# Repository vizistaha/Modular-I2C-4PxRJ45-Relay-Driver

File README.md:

# Modular-I2C-4PxRJ45-Relay-Driver
an oxrs compatible I2C-4PxRJ45-Relay-Driver board in a modular format. Inspired by 8-Channel Relay Driver Shield from Superhouse and Modular-I2CRJ45 from Austin's Creations.

rev 1 - non isolated version  
rev 2 - power circuit is fully isolated from mcu circuit by optocoupler  
rev 2_1 - output uses pluggable terminal instead of 4PxRJ45  
RJ45toTerminal - breakout board for rj45 to pluggable connector (check read me for pin mapping)

For more details about OXRS: https://oxrs.io/

Credits
-------
 * Austin's Creations <https://www.austinscreations.ca/>
 * Jonathan Oxer <https://www.superhouse.tv/>

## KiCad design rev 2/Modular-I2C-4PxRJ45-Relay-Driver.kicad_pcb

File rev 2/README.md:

# RJ45 Pinout

| Pin        | Pair       | Color        |
| ---------- |:----------:| ------------ |
| 1          | 1+         | Orange-White |
| 2          | 1-         | Orange       |
| 3          | 2+         | Green-White  |
| 6          | 2-         | Green        |
| 5          | 3+         | Blue-White   |
| 4          | 3-         | Blue         |
| 7          | 4+         | Brown-White  |
| 8          | 4-         | Brown        |

VIN Jumper Connection

| VIN        | JP1        | JP2     | JP3    |
| ---------- |:---------- | ------- | ------ |
| 24V        | VIN        | 5V      | ON     |
| 12V        | VIN        | 5V      | ON     |
| 5V         | VIN        | VIN     | OFF    |

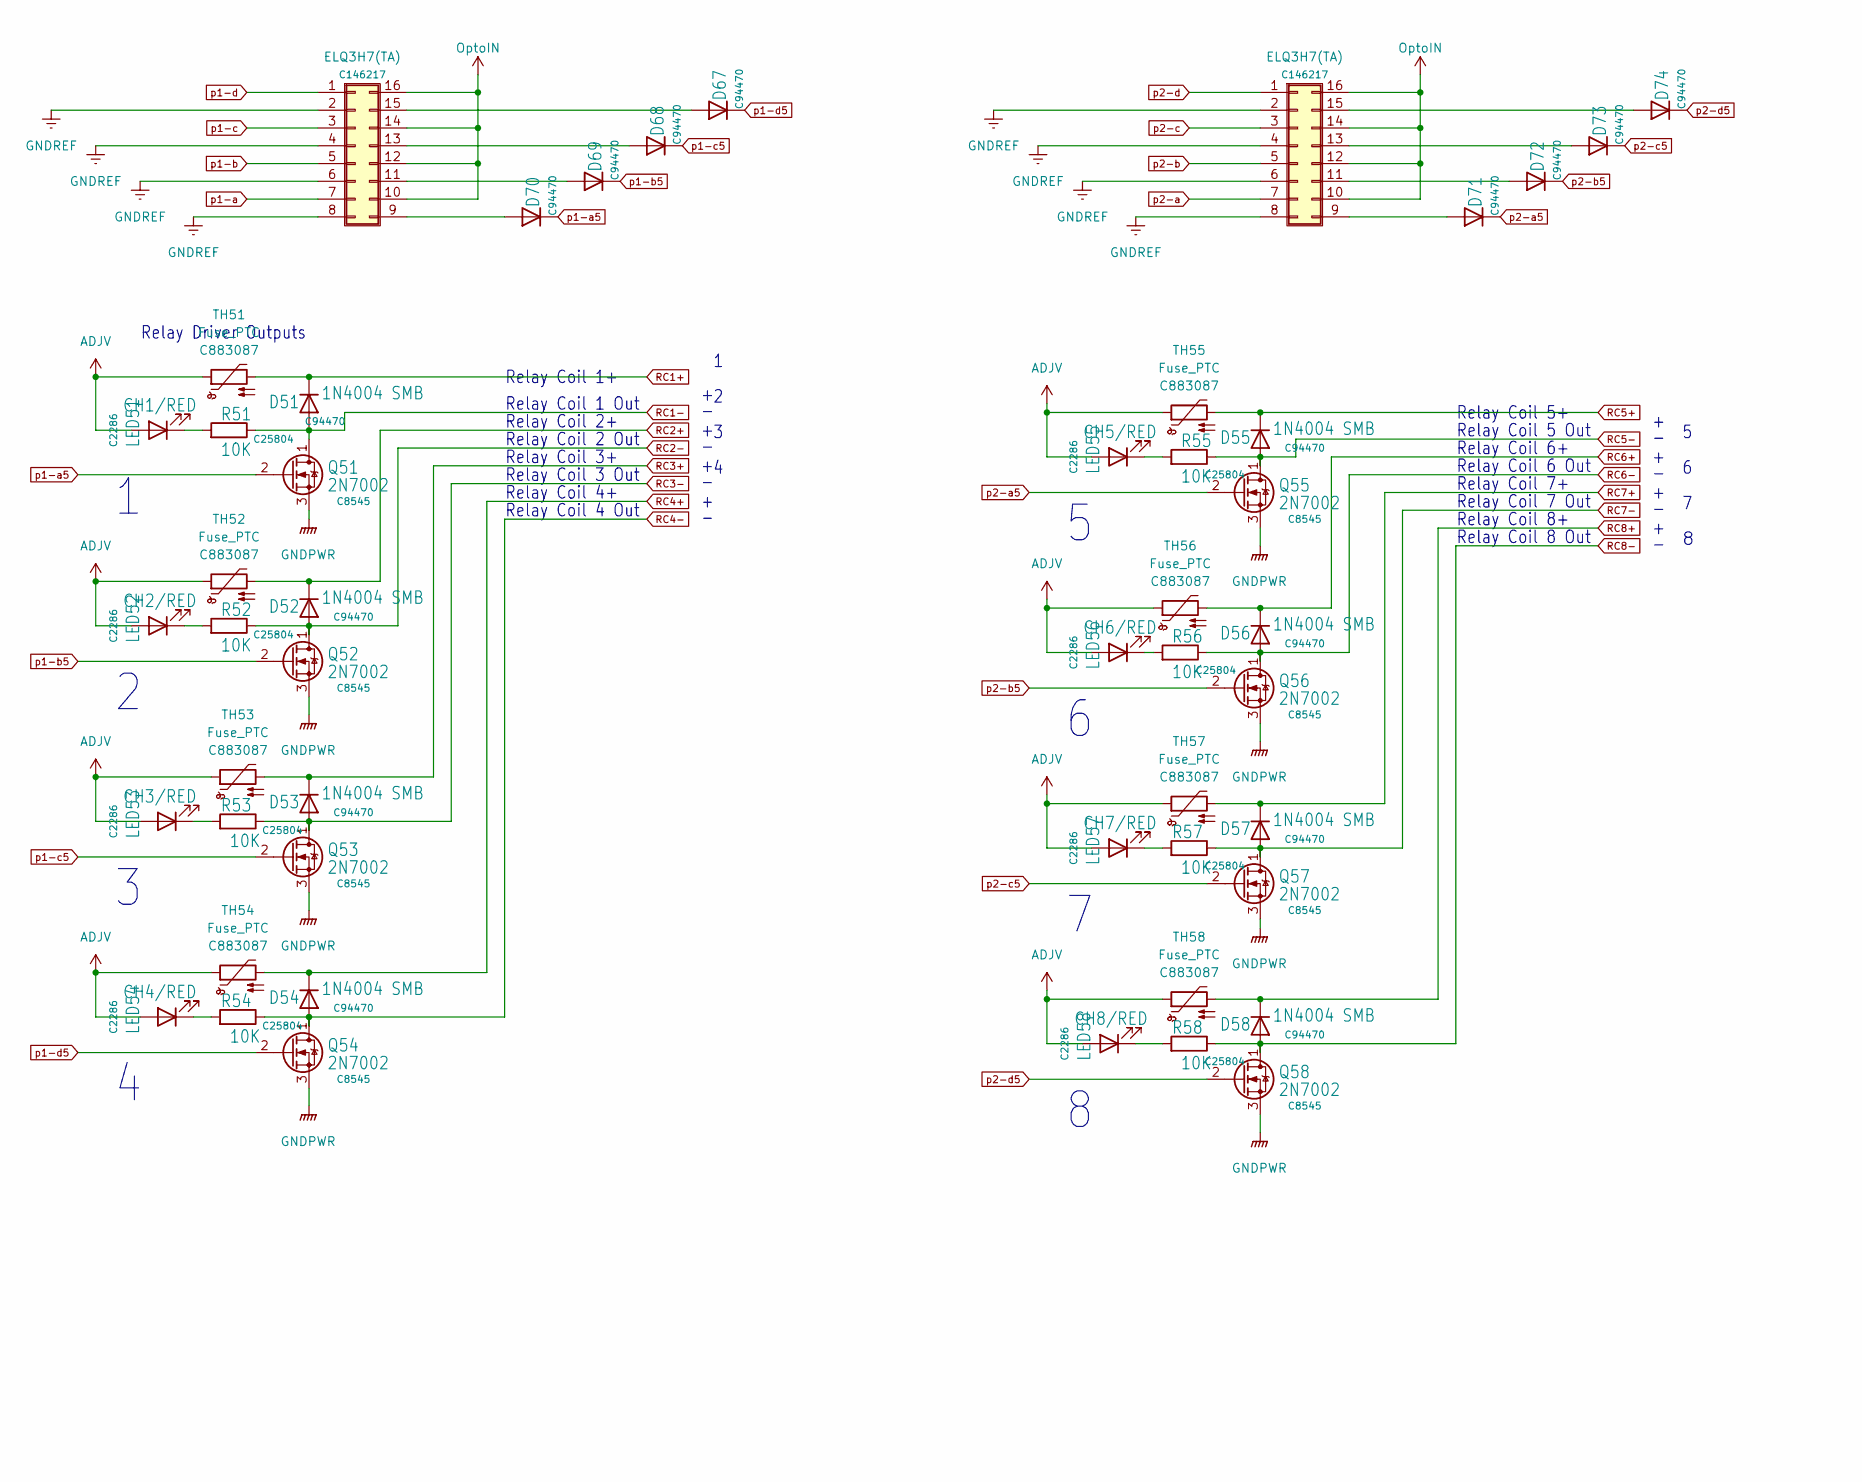
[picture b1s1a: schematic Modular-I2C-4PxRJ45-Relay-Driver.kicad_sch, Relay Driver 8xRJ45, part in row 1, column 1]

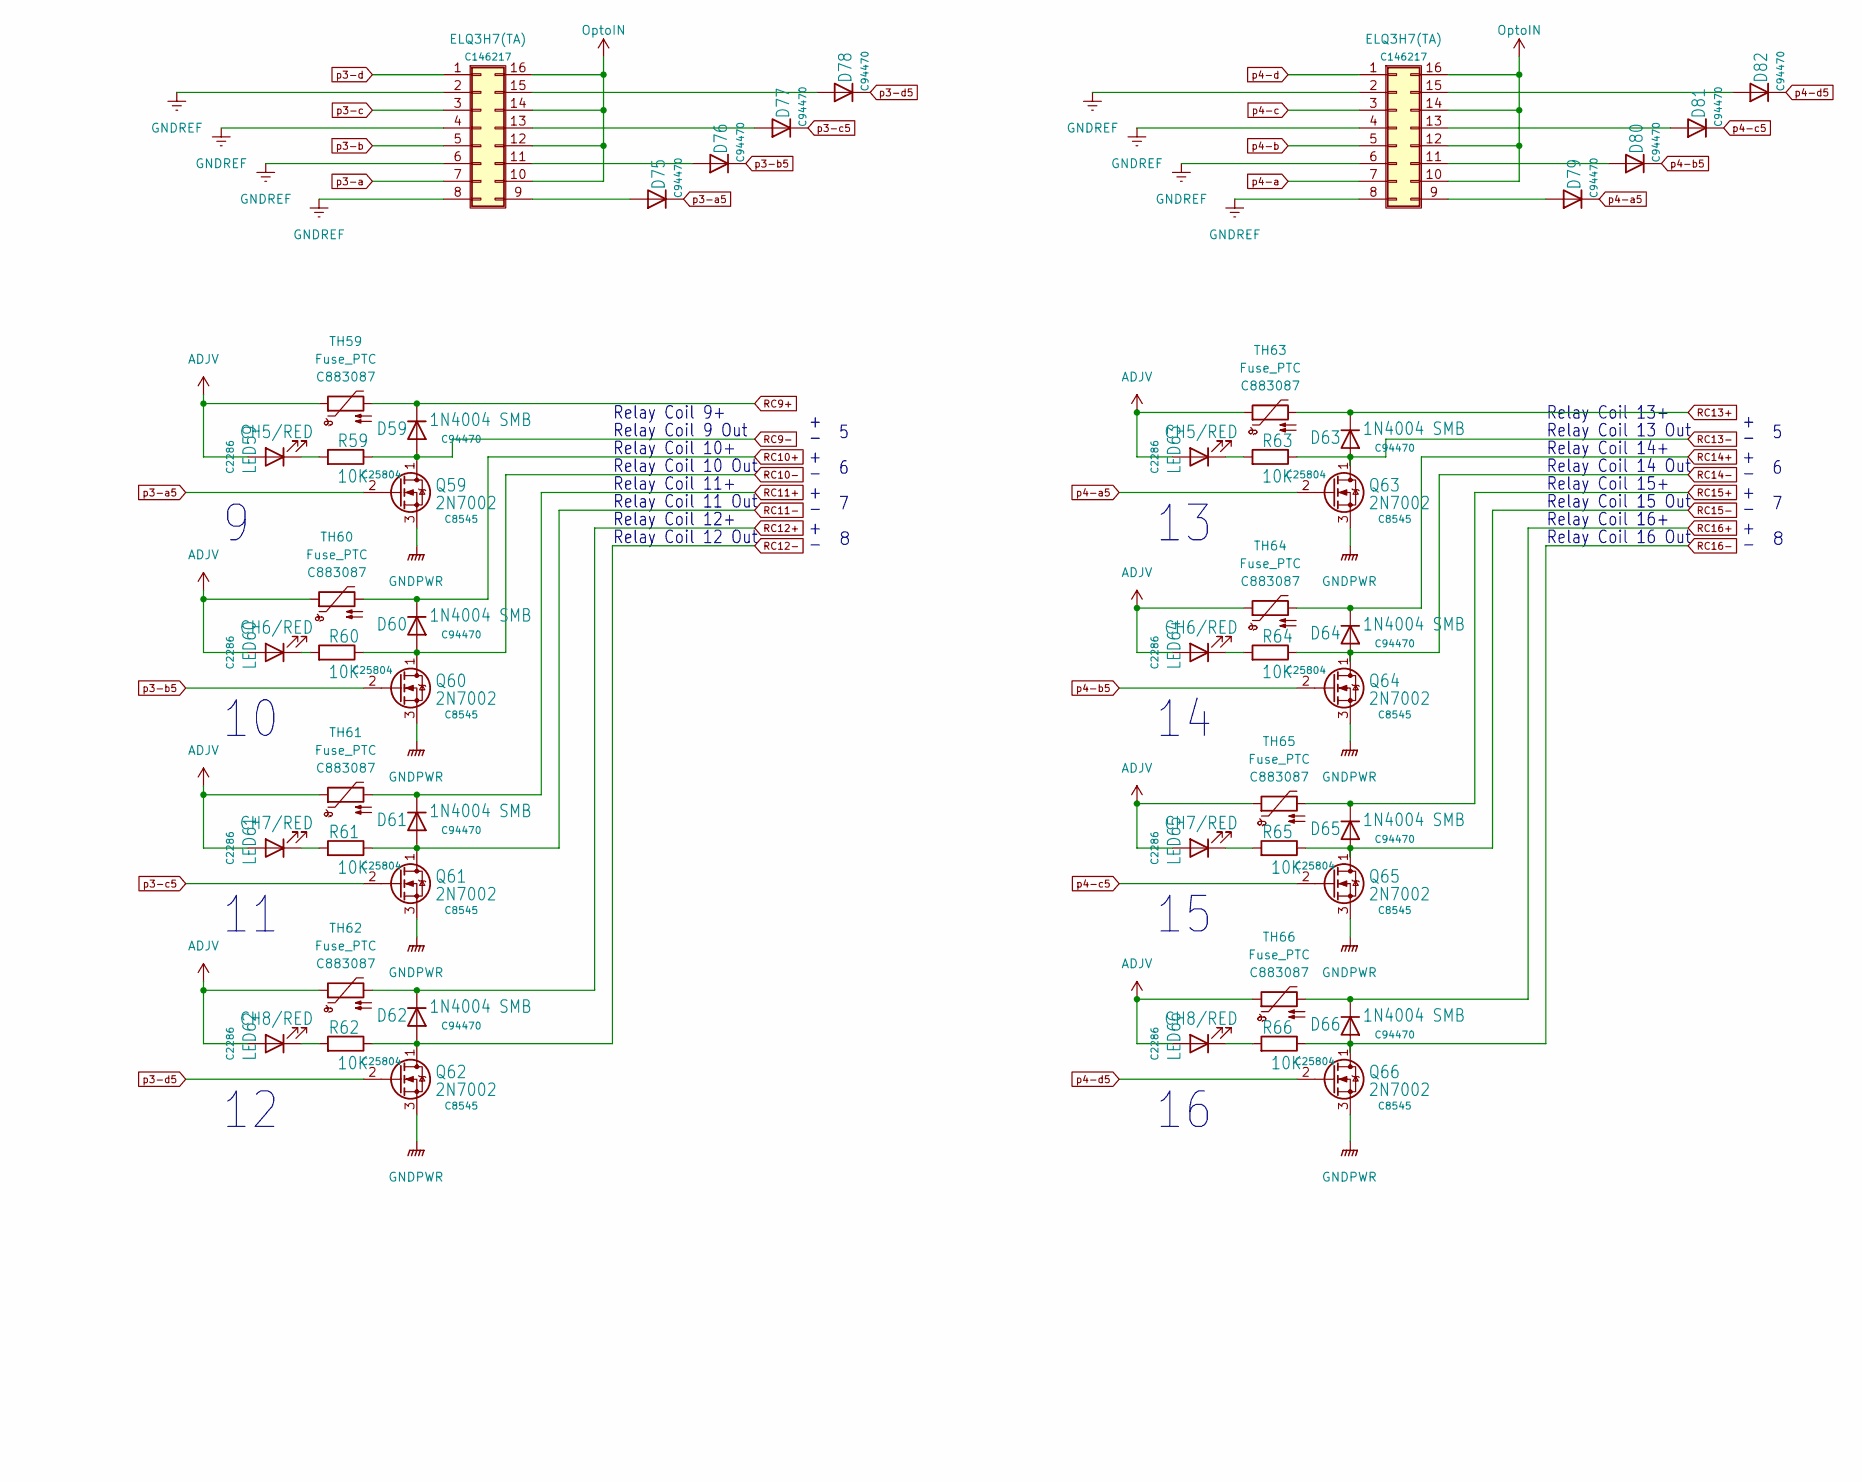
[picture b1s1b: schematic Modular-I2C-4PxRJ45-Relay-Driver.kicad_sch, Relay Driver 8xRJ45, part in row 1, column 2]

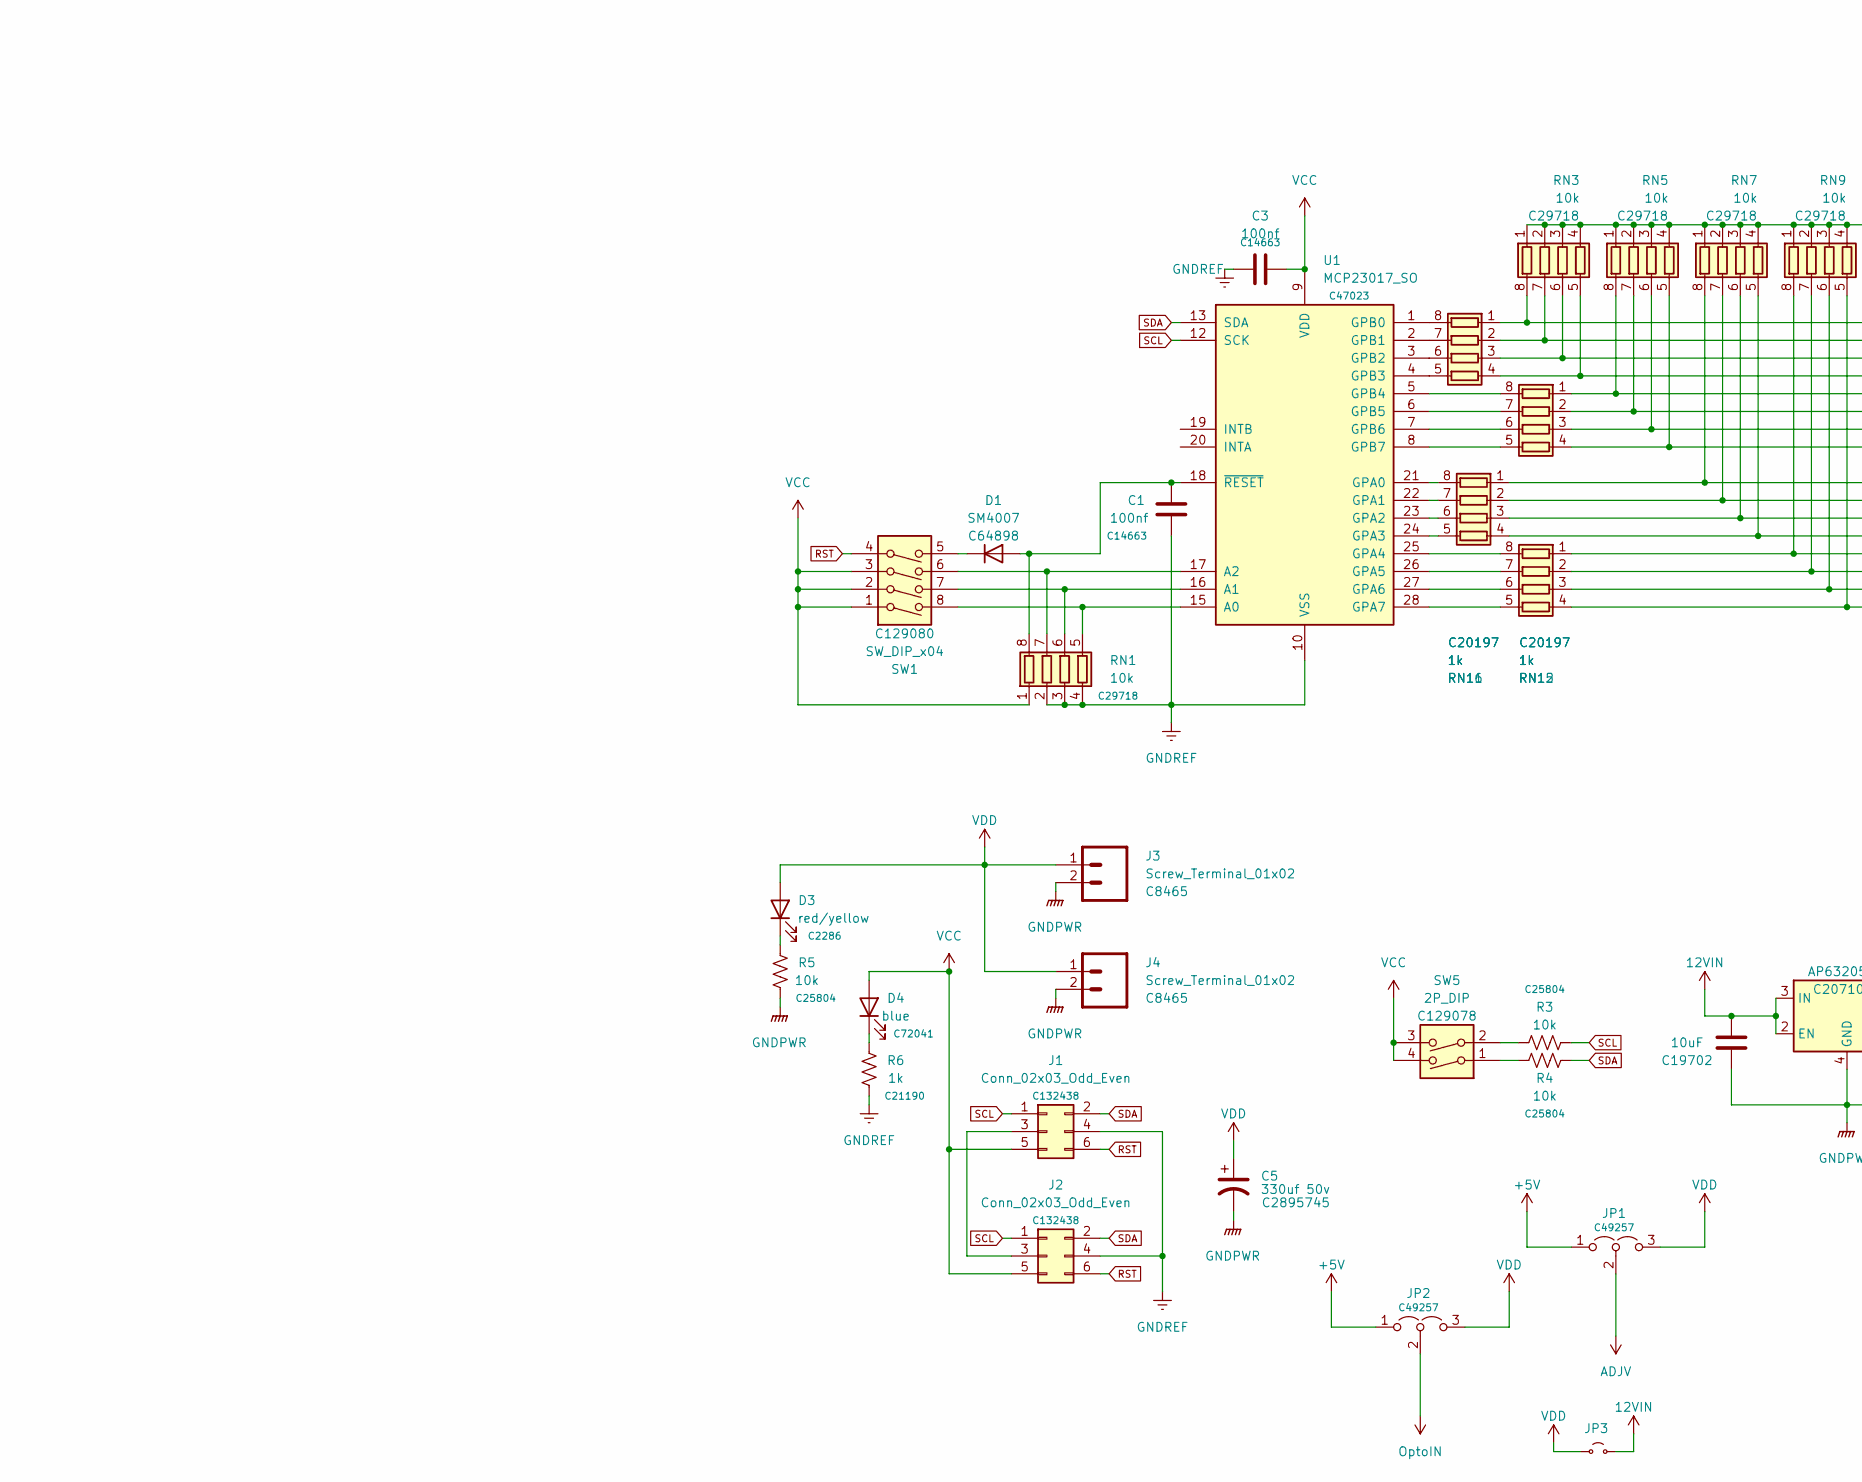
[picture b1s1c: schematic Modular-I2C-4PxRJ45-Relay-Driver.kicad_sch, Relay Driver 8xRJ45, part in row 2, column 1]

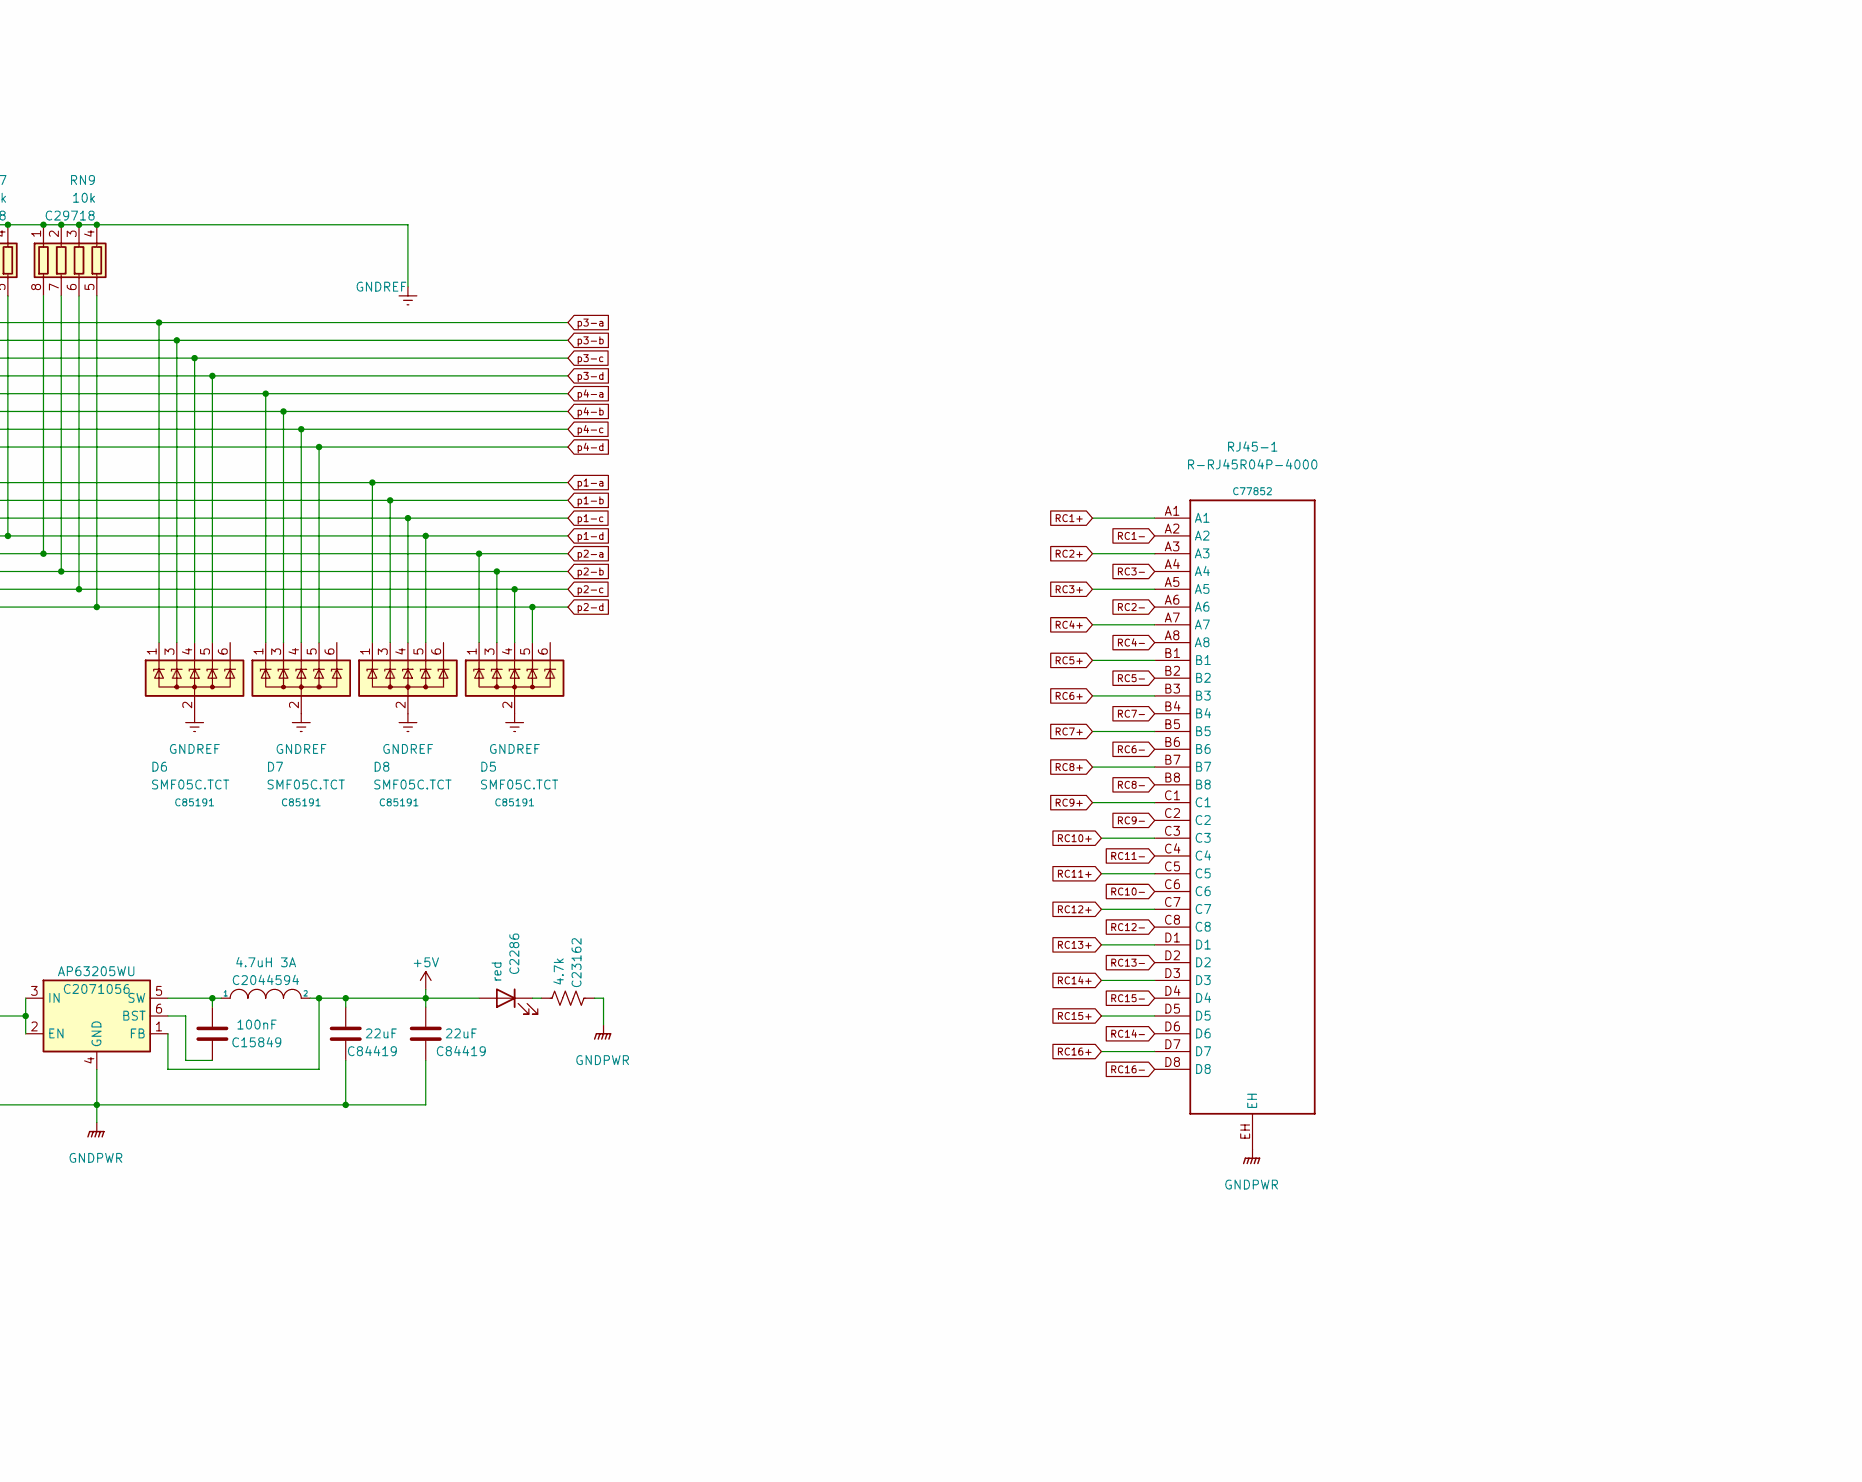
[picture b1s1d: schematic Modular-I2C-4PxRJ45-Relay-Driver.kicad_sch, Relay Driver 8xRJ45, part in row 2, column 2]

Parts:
C1, C3: 100nf; C_0603_1608Metric; LCSC C14663
C5: 330uf 50v; CP_Elec_10x10; LCSC C2895745
C6: 100nF; C_0603_1608Metric; LCSC C15849
C7, C8: 22uF; C_0603_1608Metric; LCSC C84419
C9: 10uF; C_0603_1608Metric; LCSC C19702
D1: SM4007; D_SOD-123F; LCSC C64898
D2: red; LED_0603_1608Metric; LCSC C2286
D3: red/yellow; LED_0603_1608Metric; LCSC C2286
D4: blue; LED_0603_1608Metric; LCSC C72041
D5, D6, D7, D8: SMF05C.TCT; SOT-363_SC-70-6; LCSC C85191
D51: 1N4004 SMB; D_MicroSMP; LCSC_old C727080
D52, D53, D54, D55, D56, D57, D58, D59, D60, D61, D62, D63, D64, D65, D66: 1N4004 SMB; D_MicroSMP; LCSC C94470
D67, D68, D69, D70, D71, D72, D73, D74, D75, D76, D77, D78, D79, D80, D81, D82: 1N4004 SMB; LCSC-C94470-MICROSMP_L2.2-W1.3-LS2.5-RD; LCSC_old C727080
J1, J2: Conn_02x03_Odd_Even; IDC-Header_2x03_P2.54mm_Vertical; LCSC C132438
J3, J4: Screw_Terminal_01x02; LCSC-C8465-CONN-TH_2P-P5.00_WJ500V-5.08-2P; LCSC C8465
JP1, JP2: Jumper_3_Open; PinHeader_1x03_P2.54mm_Vertical; LCSC C49257
JP3: Jumper_2_Small_Open; PinHeader_1x02_P2.54mm_Vertical; LCSC C492401
L1: 4.7uH 3A; L_6.3x6.3_H3; LCSC C2044594
LED51: CH1/RED; LED_0603_1608Metric; LCSC C2286
LED52: CH2/RED; LED_0603_1608Metric; LCSC C2286
LED53: CH3/RED; LED_0603_1608Metric; LCSC C2286
LED54: CH4/RED; LED_0603_1608Metric; LCSC C2286
LED55, LED59, LED63: CH5/RED; LED_0603_1608Metric; LCSC C2286
LED56, LED60, LED64: CH6/RED; LED_0603_1608Metric; LCSC C2286
LED57, LED61, LED65: CH7/RED; LED_0603_1608Metric; LCSC C2286
LED58, LED62, LED66: CH8/RED; LED_0603_1608Metric; LCSC C2286
Q51, Q52, Q53, Q54, Q55, Q56, Q57, Q58, Q59, Q60, Q61, Q62, Q63, Q64, Q65, Q66: 2N7002; SOT-23; LCSC C8545
R1: 4.7k; R_0603_1608Metric; LCSC C23162
R3, R4, R5: 10k; R_0603_1608Metric; LCSC C25804
R6: 1k; R_0603_1608Metric; LCSC C21190
R51, R52, R53, R54, R55, R56, R57, R58, R59, R60, R61, R62, R63, R64, R65, R66: 10K; R_0603_1608Metric; LCSC C25804
RJ45-1: R-RJ45R04P-4000; CONN-TH_DS1129-02-S80BP; LCSC C77852
RN1, RN3, RN5, RN7, RN9: 10k; R_Array_Convex_4x0603; LCSC C29718
RN11, RN12, RN15, RN16: 1k; R_Array_Convex_4x0603; LCSC C20197
SW1: SW_DIP_x04; 4P_DIP; LCSC C129080
SW5: 2P_DIP; LCSC C129078
TH51, TH52, TH53, TH54, TH55, TH56, TH57, TH58, TH59, TH60, TH61, TH62, TH63, TH64, TH65, TH66: Fuse_PTC; R_0603_1608Metric; LCSC C883087
U1: MCP23017_SO; SOIC-28W_7.5x17.9mm_P1.27mm; LCSC C47023
U2: AP63205WU; TSOT-23-6; LCSC C2071056
U3, U4, U5, U6: ELQ3H7(TA); SO-16_5.3x10.2mm_P1.27mm; LCSC C146217

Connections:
12VIN: C9.2, JP3.2 (B), U2.2 (EN), U2.3 (IN)
+5V: C7.2, C8.2, D2.2 (A), JP1.1 (A), JP2.1 (A), L1.2, U2.1 (FB)
ADJV: JP1.2 (C), LED51.2 (A), LED52.2 (A), LED53.2 (A), LED54.2 (A), LED55.2 (A), LED56.2 (A), LED57.2 (A), LED58.2 (A), LED59.2 (A), LED60.2 (A), LED61.2 (A), LED62.2 (A), LED63.2 (A), LED64.2 (A), LED65.2 (A), LED66.2 (A), TH51.1, TH52.1, TH53.1, TH54.1, TH55.1, TH56.1, TH57.1, TH58.1, TH59.1, TH60.1, TH61.1, TH62.1, TH63.1, TH64.1, TH65.1, TH66.1
GNDPWR: C5.2, C7.1, C8.1, C9.1, J3.2, J4.2, Q51.3 (S), Q52.3 (S), Q53.3 (S), Q54.3 (S), Q55.3 (S), Q56.3 (S), Q57.3 (S), Q58.3 (S), Q59.3 (S), Q60.3 (S), Q61.3 (S), Q62.3 (S), Q63.3 (S), Q64.3 (S), Q65.3 (S), Q66.3 (S), R1.1, R5.2, RJ45-1.EH, U2.4 (GND)
GNDREF: C1.2, C3.1, D5.2 (A), D6.2 (A), D7.2 (A), D8.2 (A), J1.4, J2.4, R6.2, RN1.2 (R2.1), RN1.3 (R3.1), RN1.4 (R4.1), RN3.1 (R1.1), RN3.2 (R2.1), RN3.3 (R3.1), RN3.4 (R4.1), RN5.1 (R1.1), RN5.2 (R2.1), RN5.3 (R3.1), RN5.4 (R4.1), RN7.1 (R1.1), RN7.2 (R2.1), RN7.3 (R3.1), RN7.4 (R4.1), RN9.1 (R1.1), RN9.2 (R2.1), RN9.3 (R3.1), RN9.4 (R4.1), U1.10 (VSS), U3.2, U3.4, U3.6, U3.8, U4.2, U4.4, U4.6, U4.8, U5.2, U5.4, U5.6, U5.8, U6.2, U6.4, U6.6, U6.8
unnamed: C1.1, D1.2 (A), RN1.8 (R1.2), U1.18 (~RESET)
unnamed: D1.1 (K), SW1.5
unnamed: D2.1 (K), R1.2
unnamed: D3.1 (K), R5.1
unnamed: D4.1 (K), R6.1
unnamed: D67.2 (A), U3.15
unnamed: D68.2 (A), U3.13
unnamed: D69.2 (A), U3.11
unnamed: D70.2 (A), U3.9
unnamed: D71.2 (A), U4.9
unnamed: D72.2 (A), U4.11
unnamed: D73.2 (A), U4.13
unnamed: D74.2 (A), U4.15
unnamed: D75.2 (A), U5.9
unnamed: D76.2 (A), U5.11
unnamed: D77.2 (A), U5.13
unnamed: D78.2 (A), U5.15
unnamed: D79.2 (A), U6.9
unnamed: D80.2 (A), U6.11
unnamed: D81.2 (A), U6.13
unnamed: D82.2 (A), U6.15
unnamed: J1.3, J2.3
unnamed: LED51.1 (K), R51.2
unnamed: LED52.1 (K), R52.2
unnamed: LED53.1 (K), R53.2
unnamed: LED54.1 (K), R54.2
unnamed: LED55.1 (K), R55.2
unnamed: LED56.1 (K), R56.2
unnamed: LED57.1 (K), R57.2
unnamed: LED58.1 (K), R58.2
unnamed: LED59.1 (K), R59.2
unnamed: LED60.1 (K), R60.2
unnamed: LED61.1 (K), R61.2
unnamed: LED62.1 (K), R62.2
unnamed: LED63.1 (K), R63.2
unnamed: LED64.1 (K), R64.2
unnamed: LED65.1 (K), R65.2
unnamed: LED66.1 (K), R66.2
unnamed: R3.1, SW5.2
unnamed: R4.1, SW5.1
unnamed: RN1.7 (R2.2), SW1.6, U1.17 (A2)
unnamed: RN1.6 (R3.2), SW1.7, U1.16 (A1)
unnamed: RN1.5 (R4.2), SW1.8, U1.15 (A0)
unnamed: RN11.8 (R1.2), U1.1 (GPB0)
unnamed: RN11.7 (R2.2), U1.2 (GPB1)
unnamed: RN11.6 (R3.2), U1.3 (GPB2)
unnamed: RN11.5 (R4.2), U1.4 (GPB3)
unnamed: RN12.8 (R1.2), U1.25 (GPA4)
unnamed: RN12.7 (R2.2), U1.26 (GPA5)
unnamed: RN12.6 (R3.2), U1.27 (GPA6)
unnamed: RN12.5 (R4.2), U1.28 (GPA7)
unnamed: RN15.8 (R1.2), U1.5 (GPB4)
unnamed: RN15.7 (R2.2), U1.6 (GPB5)
unnamed: RN15.6 (R3.2), U1.7 (GPB6)
unnamed: RN15.5 (R4.2), U1.8 (GPB7)
unnamed: RN16.8 (R1.2), U1.21 (GPA0)
unnamed: RN16.7 (R2.2), U1.22 (GPA1)
unnamed: RN16.6 (R3.2), U1.23 (GPA2)
unnamed: RN16.5 (R4.2), U1.24 (GPA3)
unnamed: C6.2, U2.6 (BST)
unnamed: C6.1, L1.1, U2.5 (SW)
OptoIN: JP2.2 (C), U3.10, U3.12, U3.14, U3.16, U4.10, U4.12, U4.14, U4.16, U5.10, U5.12, U5.14, U5.16, U6.10, U6.12, U6.14, U6.16
RC1+: D51.1 (K), RJ45-1.A1, TH51.2
RC1-: D51.2 (A), Q51.1 (D), R51.1, RJ45-1.A2
RC2+: D52.1 (K), RJ45-1.A3, TH52.2
RC2-: D52.2 (A), Q52.1 (D), R52.1, RJ45-1.A6
RC3+: D53.1 (K), RJ45-1.A5, TH53.2
RC3-: D53.2 (A), Q53.1 (D), R53.1, RJ45-1.A4
RC4+: D54.1 (K), RJ45-1.A7, TH54.2
RC4-: D54.2 (A), Q54.1 (D), R54.1, RJ45-1.A8
RC5+: D55.1 (K), RJ45-1.B1, TH55.2
RC5-: D55.2 (A), Q55.1 (D), R55.1, RJ45-1.B2
RC6+: D56.1 (K), RJ45-1.B3, TH56.2
RC6-: D56.2 (A), Q56.1 (D), R56.1, RJ45-1.B6
RC7+: D57.1 (K), RJ45-1.B5, TH57.2
RC7-: D57.2 (A), Q57.1 (D), R57.1, RJ45-1.B4
RC8+: D58.1 (K), RJ45-1.B7, TH58.2
RC8-: D58.2 (A), Q58.1 (D), R58.1, RJ45-1.B8
RC9+: D59.1 (K), RJ45-1.C1, TH59.2
RC9-: D59.2 (A), Q59.1 (D), R59.1, RJ45-1.C2
RC10+: D60.1 (K), RJ45-1.C3, TH60.2
RC10-: D60.2 (A), Q60.1 (D), R60.1, RJ45-1.C6
RC11+: D61.1 (K), RJ45-1.C5, TH61.2
RC11-: D61.2 (A), Q61.1 (D), R61.1, RJ45-1.C4
RC12+: D62.1 (K), RJ45-1.C7, TH62.2
RC12-: D62.2 (A), Q62.1 (D), R62.1, RJ45-1.C8
RC13+: D63.1 (K), RJ45-1.D1, TH63.2
RC13-: D63.2 (A), Q63.1 (D), R63.1, RJ45-1.D2
RC14+: D64.1 (K), RJ45-1.D3, TH64.2
RC14-: D64.2 (A), Q64.1 (D), R64.1, RJ45-1.D6
RC15+: D65.1 (K), RJ45-1.D5, TH65.2
RC15-: D65.2 (A), Q65.1 (D), R65.1, RJ45-1.D4
RC16+: D66.1 (K), RJ45-1.D7, TH66.2
RC16-: D66.2 (A), Q66.1 (D), R66.1, RJ45-1.D8
RST: J1.6, J2.6, SW1.4
SCL: J1.1, J2.1, R3.2, U1.12 (SCK)
SDA: J1.2, J2.2, R4.2, U1.13 (SDA)
VCC: C3.2, D4.2 (A), J1.5, J2.5, RN1.1 (R1.1), SW1.1, SW1.2, SW1.3, SW5.3, SW5.4, U1.9 (VDD)
VDD: C5.1, D3.2 (A), J3.1, J4.1, JP1.3 (B), JP2.3 (B), JP3.1 (A)
p1-a: D8.1 (K), RN7.8 (R1.2), RN16.1 (R1.1), U3.7
p1-a5: D70.1 (K), Q51.2 (G)
p1-b: D8.3 (K), RN7.7 (R2.2), RN16.2 (R2.1), U3.5
p1-b5: D69.1 (K), Q52.2 (G)
p1-c: D8.4 (K), RN7.6 (R3.2), RN16.3 (R3.1), U3.3
p1-c5: D68.1 (K), Q53.2 (G)
p1-d: D8.5 (K), RN7.5 (R4.2), RN16.4 (R4.1), U3.1
p1-d5: D67.1 (K), Q54.2 (G)
p2-a: D5.1 (K), RN9.8 (R1.2), RN12.1 (R1.1), U4.7
p2-a5: D71.1 (K), Q55.2 (G)
p2-b: D5.3 (K), RN9.7 (R2.2), RN12.2 (R2.1), U4.5
p2-b5: D72.1 (K), Q56.2 (G)
p2-c: D5.4 (K), RN9.6 (R3.2), RN12.3 (R3.1), U4.3
p2-c5: D73.1 (K), Q57.2 (G)
p2-d: D5.5 (K), RN9.5 (R4.2), RN12.4 (R4.1), U4.1
p2-d5: D74.1 (K), Q58.2 (G)
p3-a: D6.1 (K), RN3.8 (R1.2), RN11.1 (R1.1), U5.7
p3-a5: D75.1 (K), Q59.2 (G)
p3-b: D6.3 (K), RN3.7 (R2.2), RN11.2 (R2.1), U5.5
p3-b5: D76.1 (K), Q60.2 (G)
p3-c: D6.4 (K), RN3.6 (R3.2), RN11.3 (R3.1), U5.3
p3-c5: D77.1 (K), Q61.2 (G)
p3-d: D6.5 (K), RN3.5 (R4.2), RN11.4 (R4.1), U5.1
p3-d5: D78.1 (K), Q62.2 (G)
p4-a: D7.1 (K), RN5.8 (R1.2), RN15.1 (R1.1), U6.7
p4-a5: D79.1 (K), Q63.2 (G)
p4-b: D7.3 (K), RN5.7 (R2.2), RN15.2 (R2.1), U6.5
p4-b5: D80.1 (K), Q64.2 (G)
p4-c: D7.4 (K), RN5.6 (R3.2), RN15.3 (R3.1), U6.3
p4-c5: D81.1 (K), Q65.2 (G)
p4-d: D7.5 (K), RN5.5 (R4.2), RN15.4 (R4.1), U6.1
p4-d5: D82.1 (K), Q66.2 (G)

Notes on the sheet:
Relay Coil 4+
Relay Coil 14 Out
Relay Coil 2+
Relay Driver Outputs
Relay Coil 13+
Relay Coil 1 Out
Relay Coil 7 Out
Relay Coil 10+
Relay Coil 16 Out
Relay Coil 15 Out
Relay Coil 12+
Relay Coil 12 Out
Relay Coil 7+
Relay Coil 13 Out
Relay Coil 1+
Relay Coil 3+
Relay Coil 15+
Relay Coil 14+
Relay Coil 8+
Relay Coil 11 Out
Relay Coil 4 Out
Relay Coil 3 Out
Relay Coil 6+
Relay Coil 6 Out
Relay Coil 2 Out
Relay Coil 5+
Relay Coil 5 Out
Relay Coil 9 Out
Relay Coil 10 Out
Relay Coil 16+
Relay Coil 9+
Relay Coil 11+
Relay Coil 8 Out

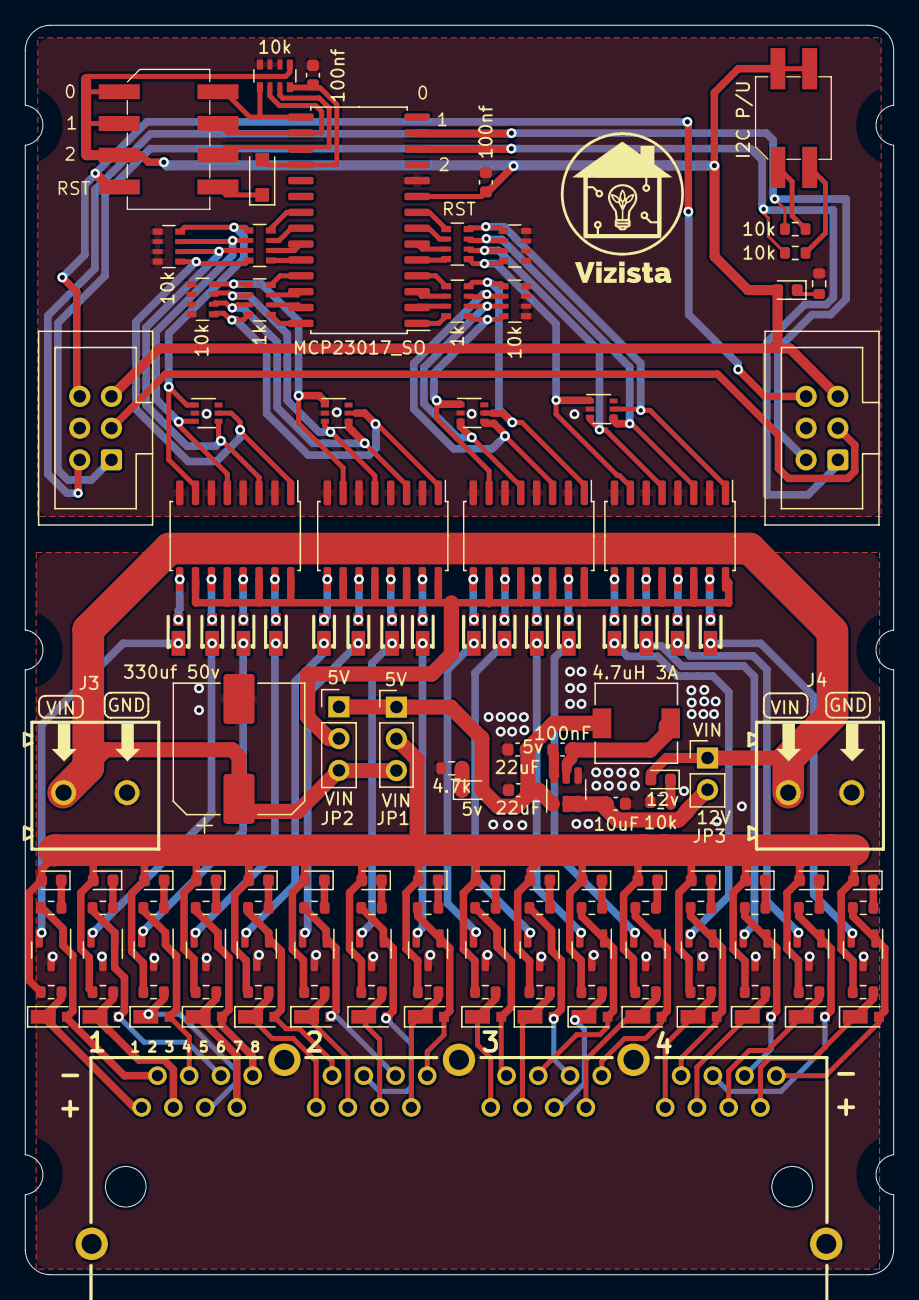
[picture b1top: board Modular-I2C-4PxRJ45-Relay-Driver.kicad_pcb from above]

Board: 2 copper layers, 69.5 x 100.0 mm, 142 parts (0 on the bottom side), 136 nets.
